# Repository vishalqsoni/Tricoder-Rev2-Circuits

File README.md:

# Star Trek Tricorder Rev2 — PCB & Schematics

> KiCad schematic and PCB layout files for the Star Trek Tricorder Rev2. The hardware is distributed across three boards — Tricorder Main, Tricorder Sensor, and Tricorder LED Array 2 — interconnected via a 20-pin FFC cable.

---

## Table of Contents

- [Board Overview](#board-overview)
- [Tricorder Main](#tricorder-main)
- [Tricorder Sensor](#tricorder-sensor)
- [Tricorder LED Array 2](#tricorder-led-array-2)
- [Interconnect](#interconnect--ffc-cable)
- [Repository Structure](#repository-structure)
- [Tools Used](#tools-used)
- [Related Repositories](#related-repositories)
- [Credits](#credits)

---

## Board Overview

The hardware is split across three dedicated PCBs to keep the design modular and assembly manageable within the compact Tricorder enclosure.

| Board | Role | Files Available |
|---|---|---|
| Tricorder Main | Central controller — ESP32S3, display, audio, touch input | Schematic + Layout |
| Tricorder Sensor | Environmental sensing, power monitoring, LED array 1 | Layout only |
| Tricorder LED Array 2 | Secondary WS2812B LED array | Schematic + Layout |

All boards are KiCad projects and communicate over a shared **I²C bus** via a **20-pin 1mm pitch FFC cable**.

---

## Tricorder Main

The Main PCB is the central control unit built around the **Seeed Studio XIAO ESP32S3**. It sits directly below the TFT display and coordinates all subsystems.

**Files:** Schematic + Layout

### Interfaces

| Interface | Protocol | Connected To |
|---|---|---|
| TFT Display (ST7735) | SPI (MOSI, SCK, CS, DC, RST) | ST7735 1.8" TFT |
| Audio Module (JQ6500) | UART (TX/RX) | JQ6500 |
| GPIO Expander (MCP23008) | I²C (SDA/SCL) | TTP223 touch inputs ×6 |
| LED Array — Primary | Single-wire (WS2812B protocol) | WS2812B LEDs |
| FFC Connector | 20-pin, 1mm pitch | Tricorder Sensor board |

### Key ICs

| IC / Module | Function |
|---|---|
| Seeed Studio XIAO ESP32S3 | Main microcontroller |
| MCP23008 | I²C GPIO expander for touch input routing |
| JQ6500 | UART audio playback module |
| TTP223 ×6 | Capacitive touch sensors |
| WS2812B (2020) | Addressable RGB LEDs — primary array |

---

## Tricorder Sensor

The Sensor Panel contains all environmental sensing and power monitoring components, along with LED Array 1. It connects to the Main PCB entirely over the FFC cable.

**Files:** Layout only

### Interfaces

| Interface | Protocol | Connected To |
|---|---|---|
| Environmental Sensor (BME280) | I²C | Shared I²C bus |
| Power Monitor (INA219) | I²C | Shared I²C bus |
| LED Array 1 | Single-wire (WS2812B protocol) | WS2812B LEDs |
| FFC Connector | 20-pin, 1mm pitch | Tricorder Main board |

### Key ICs

| IC / Module | Function |
|---|---|
| DFRobot BME280 | Temperature, pressure, and altitude sensing |
| INA219 | Voltage, current, and power monitoring |
| WS2812B (2020) | Addressable RGB LEDs — array 1 |

---

## Tricorder LED Array 2

A dedicated board for the secondary WS2812B LED array.

**Files:** Schematic + Layout

### Specifications

| Parameter | Value |
|---|---|
| PCB Material | FR4 |
| Board Thickness | 0.6 mm |

### Key IC

| IC / Module | Function |
|---|---|
| WS2812B (2020) | Addressable RGB LEDs — array 2 |

---

## Interconnect — FFC Cable

All boards communicate over a **20-pin, 1mm pitch FFC cable**, which carries:

| Signal Group | Lines |
|---|---|
| Power | VCC, GND |
| I²C Bus | SDA, SCL |
| LED Control | WS2812B data line |
| Miscellaneous | Additional control and status signals |

Using FFC keeps internal wiring clean, reduces assembly complexity, and allows each board to be removed or replaced independently.

---

## Repository Structure

```
tricorder-rev2-circuits/
│
├── tricorder-main/
│   ├── tricorder-main.kicad_pro
│   ├── tricorder-main.kicad_sch
│   ├── tricorder-main.kicad_pcb
│   └── gerbers/
│
├── tricorder-sensor/
│   ├── tricorder-sensor.kicad_pro
│   ├── tricorder-sensor.kicad_pcb
│   └── gerbers/
│
├── tricorder-led-array-2/
│   ├── tricorder-led-array-2.kicad_pro
│   ├── tricorder-led-array-2.kicad_sch
│   ├── tricorder-led-array-2.kicad_pcb
│   └── gerbers/
│
└── docs/
    └── block-diagram.png
```

---

## Tools Used

| Tool | Purpose |
|---|---|
| [KiCad](https://www.kicad.org/) | Schematic capture and PCB layout |

---

## Related Repositories

| Repository | Contents |
|---|---|
| [Tricorder Rev2 — Firmware](https://github.com/vishalqsoni/Tricoder-Rev2/tree/main) | Arduino firmware, UI, sensors, animations |
| [Tricorder Rev2 — 3D Models](#) | Enclosure and mechanical files |

---

## Credits

- **PCB Design & Hardware** — [Vishal Soni](https://github.com/vishalqsoni)
- **3D Printing** — [JustWay](https://justway3d.com)
- **Firmware**- [Vishal Soni](https://github.com/vishalqsoni)

---

## License

MIT License — see [LICENSE](LICENSE) for details.

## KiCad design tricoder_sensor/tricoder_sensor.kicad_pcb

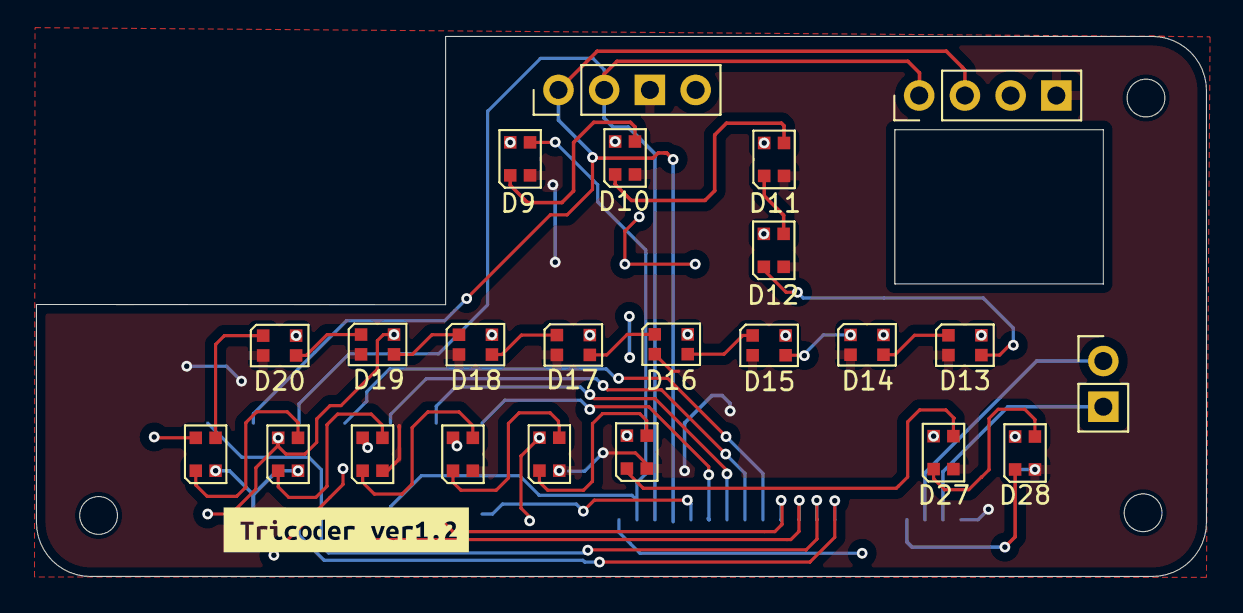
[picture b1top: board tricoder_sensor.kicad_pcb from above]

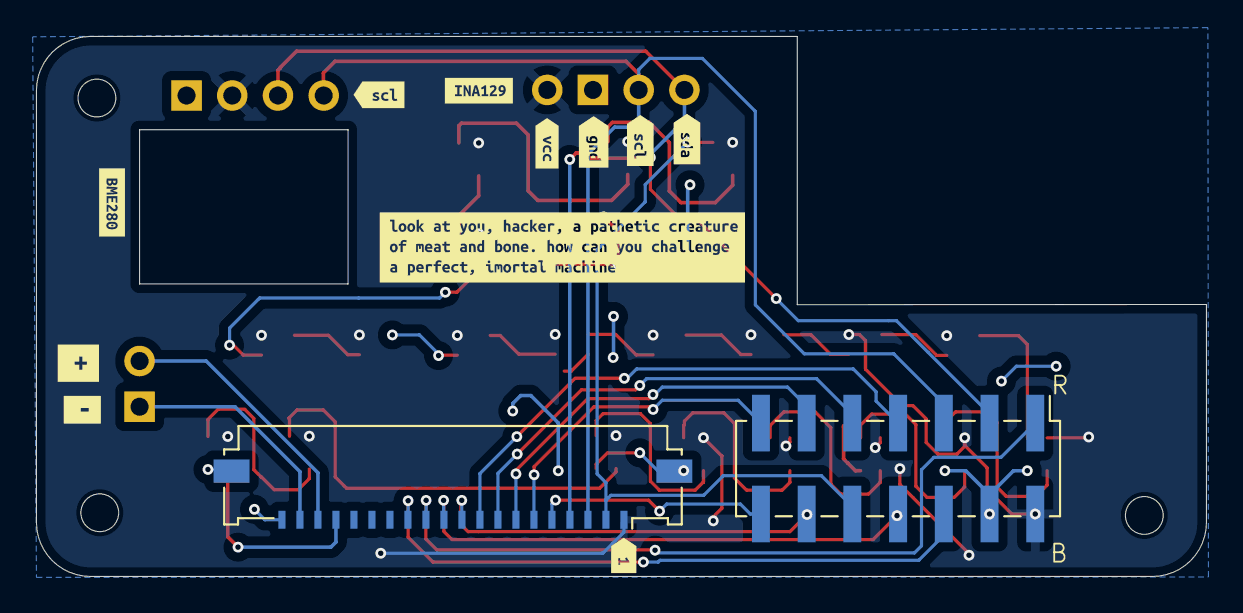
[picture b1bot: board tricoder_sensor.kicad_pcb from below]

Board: 2 copper layers, 65.0 x 30.0 mm, 32 parts (11 on the bottom side), 2 nets.

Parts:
D1, D1#2, D1#3, D1#4, D1#5, D1#6, D1#7, D1#8, D1#9, D1#10, D13, D14, D15, D16, D17, D18, D19, D20, D27, D28: WS2812B-2020; LED_WS2812B-2020_PLCC4_2.0x2.0mm
kibuzzard-69B7CB67: G***; kibuzzard-69B7CB67
kibuzzard-69B7CB86: G***; kibuzzard-69B7CB86
kibuzzard-69B7CBEE: G***; kibuzzard-69B7CBEE
kibuzzard-69B7CBF3: G***; kibuzzard-69B7CBF3
kibuzzard-69B7CBF9: G***; kibuzzard-69B7CBF9
kibuzzard-69B7CC2E: G***; kibuzzard-69B7CC2E
kibuzzard-69B7CDD1: G***; kibuzzard-69B7CDD1
kibuzzard-69B7CE0B: G***; kibuzzard-69B7CE0B
kibuzzard-69B8F494: G***; kibuzzard-69B8F494
kibuzzard-69B90B5B: G***; kibuzzard-69B90B5B
kibuzzard-69B90B55: G***; kibuzzard-69B90B55
kibuzzard-69B957A1: G***; kibuzzard-69B957A1

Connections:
/GND: D1.2 (VSS), D1#2.2 (VSS), D1#3.2 (VSS), D1#4.2 (VSS), D1#5.2 (VSS), D1#6.2 (VSS), D1#7.2 (VSS), D1#8.2 (VSS), D1#9.2 (VSS), D1#10.2 (VSS), D13.2 (VSS), D14.2 (VSS), D15.2 (VSS), D16.2 (VSS), D17.2 (VSS), D18.2 (VSS), D19.2 (VSS), D20.2 (VSS), D27.2 (VSS), D28.2 (VSS)
/VCC: D1.4 (VDD), D1#2.4 (VDD), D1#3.4 (VDD), D1#4.4 (VDD), D1#5.4 (VDD), D1#6.4 (VDD), D1#7.4 (VDD), D1#8.4 (VDD), D1#9.4 (VDD), D1#10.4 (VDD), D13.4 (VDD), D14.4 (VDD), D15.4 (VDD), D16.4 (VDD), D17.4 (VDD), D18.4 (VDD), D19.4 (VDD), D20.4 (VDD), D27.4 (VDD), D28.4 (VDD)

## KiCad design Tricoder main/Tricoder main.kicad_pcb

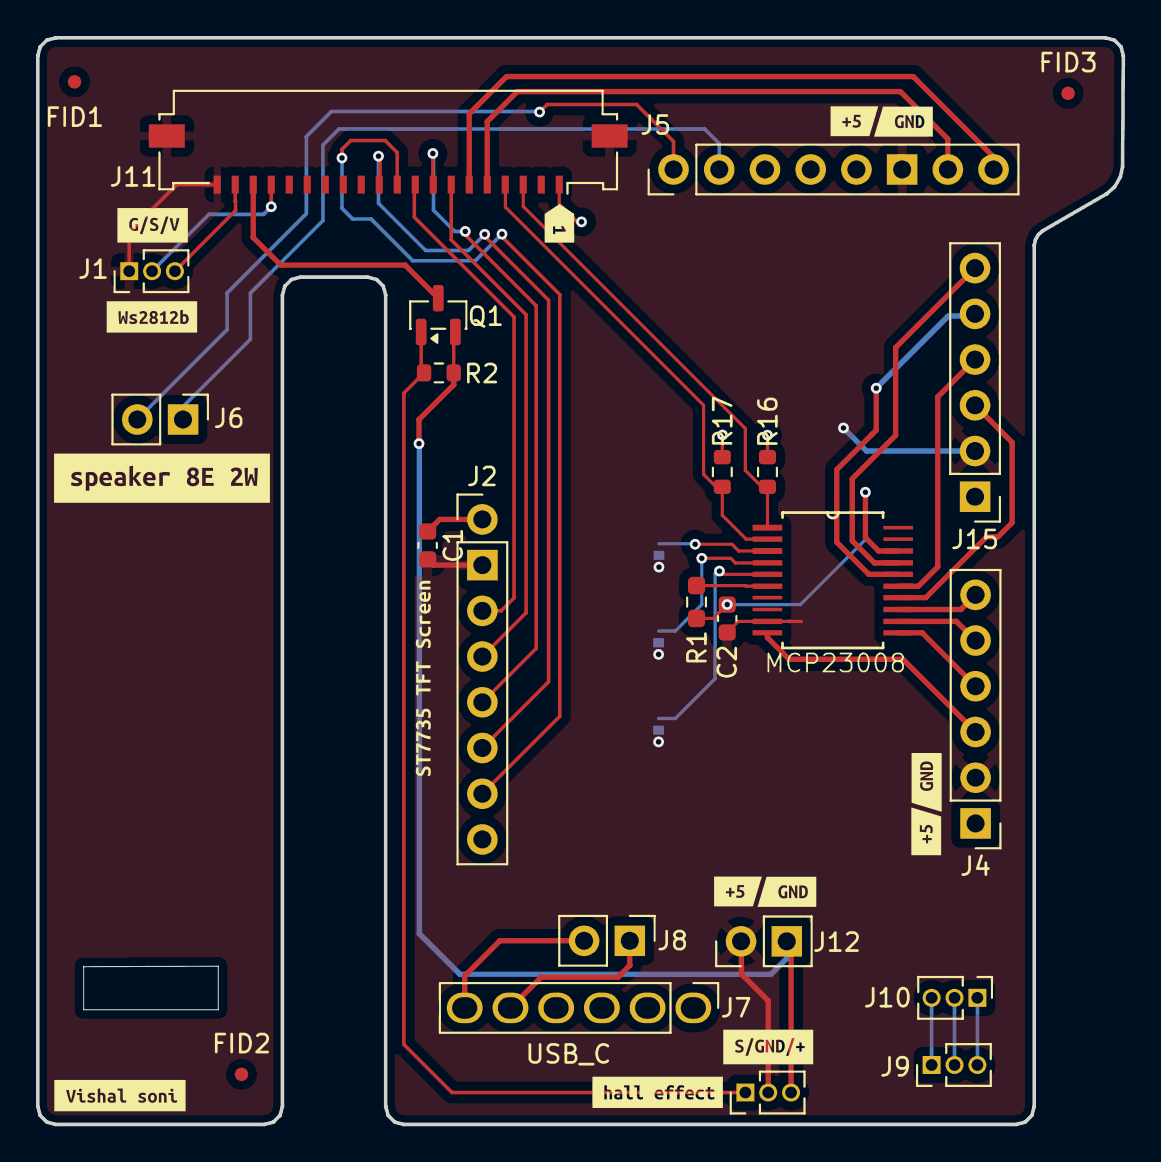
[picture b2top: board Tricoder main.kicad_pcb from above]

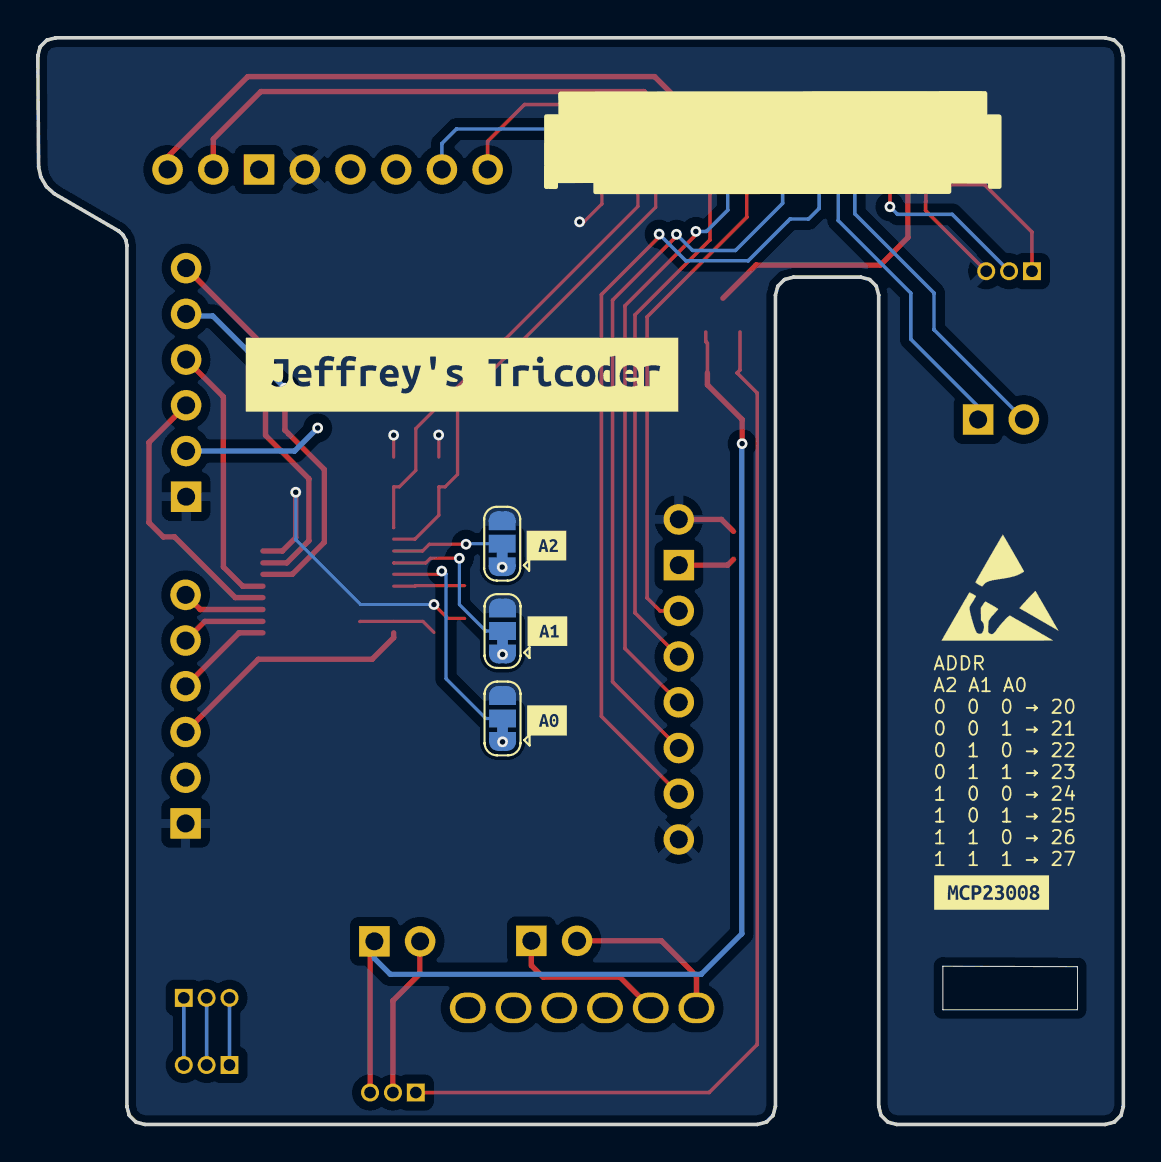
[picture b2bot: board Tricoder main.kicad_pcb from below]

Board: 2 copper layers, 60.3 x 60.4 mm, 46 parts (8 on the bottom side), 34 nets.

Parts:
C1, C2: 0.1uF; C_0603_1608Metric
FID1, FID2, FID3: Fiducial; Fiducial_0.75mm_Mask1.5mm
J1: WS2812B; PinHeader_1x03_P1.27mm_Vertical
J2: TFT_Screen; PinHeader_1x08_P2.54mm_Vertical
J4: touch_p1; PinHeader_1x06_P2.54mm_Vertical
J5: JQ6500; PinHeader_1x08_P2.54mm_Vertical
J6: speaker; PinHeader_1x02_P2.54mm_Vertical
J7: usbC; PinHeader_1x06_P2.54mm_Vertical
J8: battery_charging; PinHeader_1x02_P2.54mm_Vertical
J9, J10: charging indicator; PinHeader_1x03_P1.27mm_Vertical
J11: ffc-ffp; Molex_200528-0200_1x20-1MP_P1.00mm_Horizontal
J12: battery_output; PinHeader_1x02_P2.54mm_Vertical
J13: Hall Effect; PinHeader_1x03_P1.27mm_Vertical
J15: touch_p2; PinHeader_1x06_P2.54mm_Vertical
JP7: U1_A0; SolderJumper-3_P1.3mm_Bridged12_RoundedPad1.0x1.5mm
JP9: U1_A1; SolderJumper-3_P1.3mm_Bridged12_RoundedPad1.0x1.5mm
JP12: U1_A2; SolderJumper-3_P1.3mm_Bridged12_RoundedPad1.0x1.5mm
Q1: AO3407A; SOT-23
R1: 10K; R_0603_1608Metric_Pad0.98x0.95mm_HandSolder
R2: 10k; R_0603_1608Metric
R16, R17: 4K7; R_0603_1608Metric
U2: MCP23008-xSO; SOP65P780X200-20N
kibuzzard-69B1E323: G***; kibuzzard-69B1E323
kibuzzard-69B9A5BA: G***; kibuzzard-69B9A5BA
kibuzzard-69B9A5CD: G***; kibuzzard-69B9A5CD
kibuzzard-69B9A650: G***; kibuzzard-69B9A650
kibuzzard-69B996E9, kibuzzard-69B996E9#2, kibuzzard-69B996E9#3: G***; kibuzzard-69B996E9
kibuzzard-69B99707, kibuzzard-69B99707#2, kibuzzard-69B99707#3: G***; kibuzzard-69B99707
kibuzzard-69BA1AA8: G***; kibuzzard-69BA1AA8
kibuzzard-69BA1B42: G***; kibuzzard-69BA1B42
kibuzzard-69BA2D04: G***; kibuzzard-69BA2D04
kibuzzard-69BA573E: G***; kibuzzard-69BA573E
kibuzzard-69BA5641: G***; kibuzzard-69BA5641
kibuzzard-69BA5720: G***; kibuzzard-69BA5720
kibuzzard-69BA5749: G***; kibuzzard-69BA5749
kibuzzard-69BA5815: G***; kibuzzard-69BA5815
kibuzzard-69BA5933: G***; kibuzzard-69BA5933

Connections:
+5V: C1.1, C2.1, J1.3, J2.1, J2.8, J4.1, J5.5, J11.1, J11.19, J15.1, JP7.3 (B), JP9.3 (B), JP12.3 (B), R1.2, R16.1, R17.1, U2.18 (VDD)
/Battery: J12.2, J13.3, Q1.2 (S), R2.2
/CS_TFT: J2.3, J11.9
/DC_TFT: J2.5, J11.8
/Hall_Effect: J13.1, Q1.1 (G), R2.1
/INA219+: J11.18, Q1.3 (D)
/JQ6500_RX: J5.8, J11.6
/JQ6500_TX: J5.7, J11.5
/MOSI/SDA_TFT: J2.6, J11.11
/RESET_TFT: J2.4, J11.7
/SCK_TFT: J2.7, J11.10
/SCL: J11.3, R16.2, U2.1 (SCL)
/SDA: J11.4, R17.2, U2.2 (SDA)
/U1_0: J4.3, U2.10 (GP0)
/U1_1: J4.4, U2.11 (GP1)
/U1_2: J4.5, U2.12 (GP2)
/U1_3: J4.6, U2.13 (GP3)
/U1_4: J15.3, U2.14 (GP4)
/U1_5: J15.4, U2.15 (GP5)
/U1_6: J15.5, U2.16 (GP6)
/U1_7: J15.6, U2.17 (GP7)
/U1_A0: JP7.2 (C), U2.5 (A0)
/U1_A1: JP9.2 (C), U2.4 (A1)
/U1_A2: JP12.2 (C), U2.3 (A2)
/WS2812B: J1.2, J11.17
GND: C1.2, C2.2, J1.1, J2.2, J4.2, J5.6, J11.20, J11.21, J11.22, J12.1, J13.2, J15.2, JP7.1 (A), JP9.1 (A), JP12.1 (A), U2.9 (VSS)
unnamed: J5.1, J6.2
unnamed: J5.2, J6.1
unnamed: J7.5, J8.1
unnamed: J7.6, J8.2
unnamed: J9.3, J10.1
unnamed: J9.2, J10.2
unnamed: J9.1, J10.3
unnamed: R1.1, U2.6 (~RESET)

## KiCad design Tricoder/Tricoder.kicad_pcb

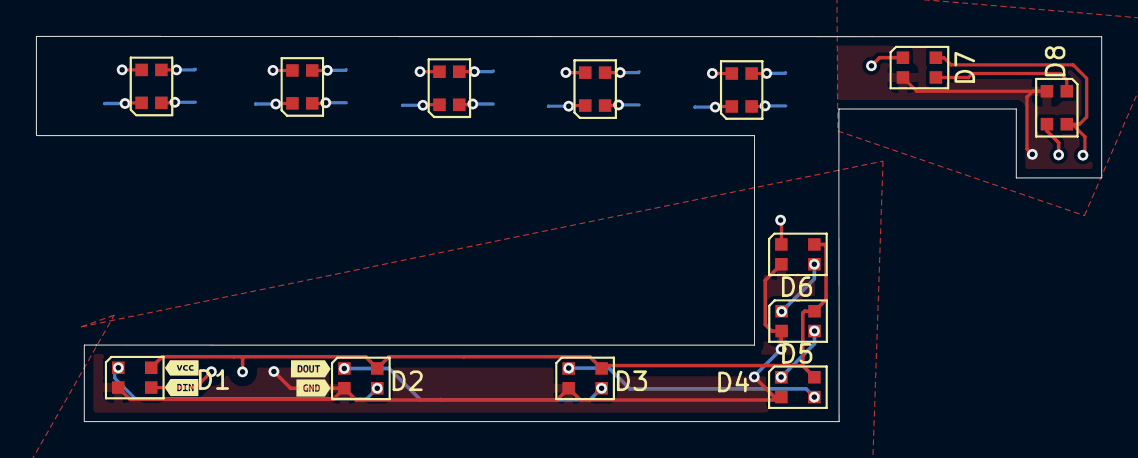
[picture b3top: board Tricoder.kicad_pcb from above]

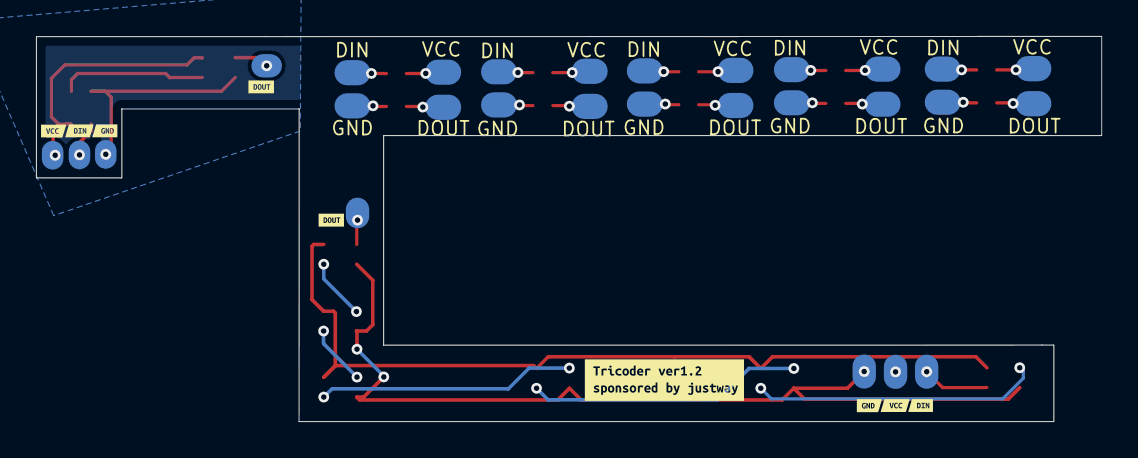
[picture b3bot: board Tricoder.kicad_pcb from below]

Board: 2 copper layers, 59.2 x 21.4 mm, 26 parts (9 on the bottom side), 9 nets.

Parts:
D1, D1#2, D1#3, D1#4, D1#5, D1#6, D2, D3, D4, D5, D6, D7, D8: WS2812B-2020; LED_WS2812B-2020_PLCC4_2.0x2.0mm
kibuzzard-69B3FD8B: G***; kibuzzard-69B3FD8B
kibuzzard-69B3FDA1: G***; kibuzzard-69B3FDA1
kibuzzard-69B452CC: G***; kibuzzard-69B452CC
kibuzzard-69B452F6, kibuzzard-69B452F6#2: G***; kibuzzard-69B452F6
kibuzzard-69B455A9: G***; kibuzzard-69B455A9
kibuzzard-69B4041F: G***; kibuzzard-69B4041F
kibuzzard-69B4043D: G***; kibuzzard-69B4043D
kibuzzard-69B4529B: G***; kibuzzard-69B4529B
kibuzzard-69B5913D: G***; kibuzzard-69B5913D
kibuzzard-69B45234: G***; kibuzzard-69B45234
kibuzzard-69B59132: G***; kibuzzard-69B59132
kibuzzard-69B59139: G***; kibuzzard-69B59139

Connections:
/DIN: D1#4.3 (DIN), D8.3 (DIN)
/DOUT: D6.1 (DOUT), D7.1 (DOUT)
/GND: D1#4.2 (VSS), D2.2 (VSS), D3.2 (VSS), D4.2 (VSS), D5.2 (VSS), D6.2 (VSS), D7.2 (VSS), D8.2 (VSS)
/VCC: D1#4.4 (VDD), D2.4 (VDD), D3.4 (VDD), D4.4 (VDD), D5.4 (VDD), D6.4 (VDD), D8.4 (VDD)
unnamed: D1#4.1 (DOUT), D2.3 (DIN)
unnamed: D2.1 (DOUT), D3.3 (DIN)
unnamed: D3.1 (DOUT), D4.3 (DIN)
unnamed: D4.1 (DOUT), D5.3 (DIN)
unnamed: D5.1 (DOUT), D6.3 (DIN)
